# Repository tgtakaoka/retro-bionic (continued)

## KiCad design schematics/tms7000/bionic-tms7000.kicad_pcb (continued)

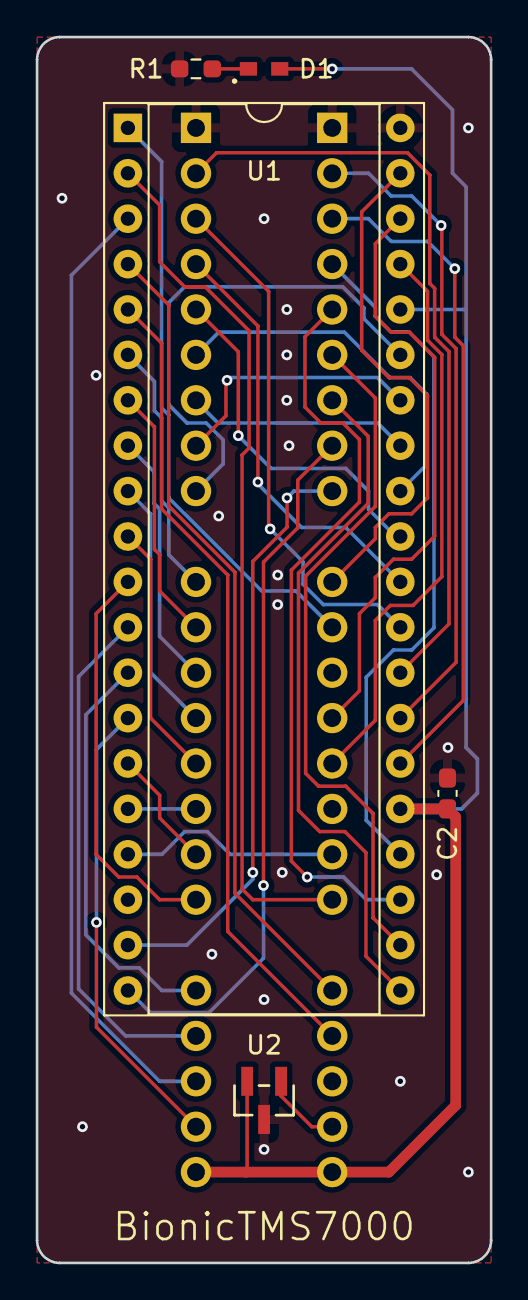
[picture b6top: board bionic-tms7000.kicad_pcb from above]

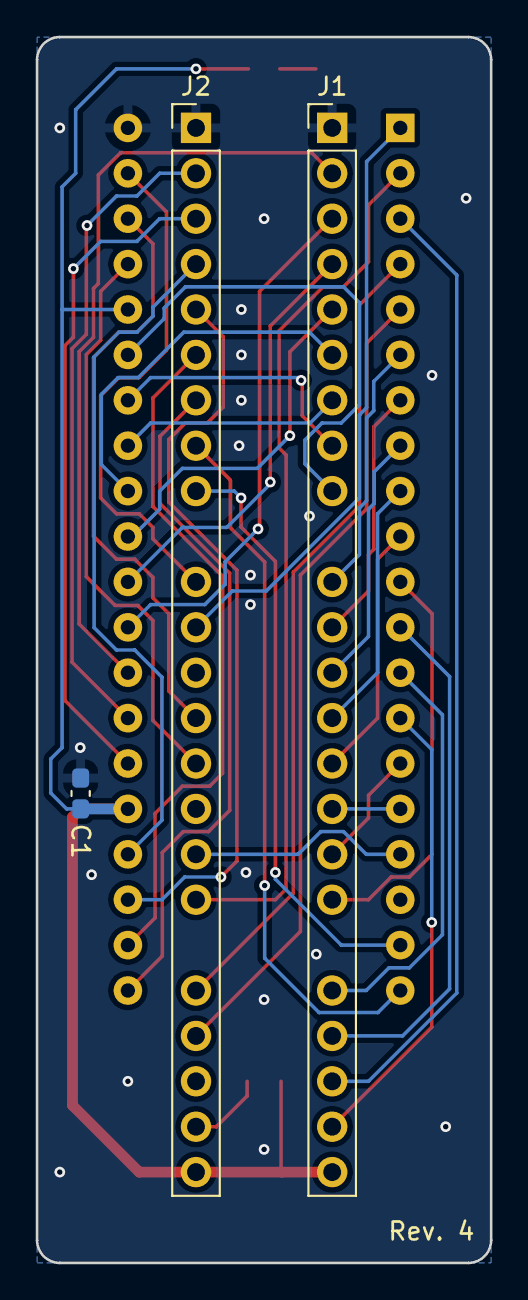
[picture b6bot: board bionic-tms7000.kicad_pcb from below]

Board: 2 copper layers, 25.4 x 68.6 mm, 8 parts (3 on the bottom side), 40 nets.
